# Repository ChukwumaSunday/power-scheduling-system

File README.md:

# Proposal/Report on Power Scheduling Project Using LDR with Arduino Nano for Solar Energy Management

Introduction
Energy management is a crucial aspect of modern office operations, especially with the growing need for sustainable energy solutions. This project outlines the design and implementation of a power scheduling system that uses an Arduino Nano, Light Dependent Resistor (LDR), DS1307 Real-Time Clock (RTC) module, and relays to optimize the use of solar energy in carrying heavy electrical loads during periods of high sunlight intensity. The system also incorporates a 2x16 Liquid Crystal Display (LCD) for real-time data visualization and a user interface with five control buttons for manual adjustments.

Objective
The primary objective of this project is to implement an automated system that shifts heavy electrical loads in an office setting to solar power when sunlight intensity is sufficient. This will minimize dependence on conventional grid power, reduce energy costs, and promote the use of renewable energy.

System Components
1. Arduino Nano: The microcontroller used to process sensor data and control the relays.
2. LDR (Light Dependent Resistor): A sensor used to measure sunlight intensity. The system uses its input to determine when sufficient sunlight is available to switch loads to solar energy.
3. DS1307 RTC Module: Provides accurate time tracking, enabling the system to record start time, date, and manage scheduled tasks.
4. 12V DC Relay and AC Relay: These relays act as switches for controlling the AC-powered heavy loads. The DC relay activates the AC relay, allowing it to handle the higher voltage loads.
5. 2x16 LCD Display: Used for displaying real-time data such as sunlight intensity, load status, and current time.
6. 5-Button Interface (Up, Down, Left, Right, Select): These buttons allow for manual adjustments, navigation of the menu, and control of the system settings.
7. Solar Panel and Battery: The solar panel generates the energy, while the battery stores excess energy for later use.

System Design
The power scheduling system is designed to operate as follows:

												The Schematics

												The Board Layout

												The Board Front View

												The Board Back View

LDR-Based Sunlight Monitoring
The LDR is connected to the Arduino Nano to measure the ambient light intensity. When sunlight is intense enough, typically indicated by an analog voltage value crossing a predefined threshold, the system activates the relays to switch the heavy loads to solar power.

Relay Control
The 12V DC relay is used to switch the AC relay, which controls the connection of heavy electrical loads to the solar power system. When sufficient sunlight is detected, the Arduino activates the DC relay, which in turn energizes the AC relay, allowing heavy office appliances such as air conditioners or industrial lighting systems to run on solar power.

Real-Time Clock for Scheduling
The DS1307 RTC module is employed to keep track of the date and time. This allows the system to monitor power consumption periods, maintain a record of when loads are shifted to solar energy, and ensure that power switching happens during predefined hours of operation. 

The RTC is also crucial for scheduled load management, ensuring that the system operates within the designated timeframes to prevent unnecessary switching during nighttime or low sunlight conditions.

User Interface and LCD Display
The 2x16 LCD displays the current system status, including:
- Sunlight intensity level
- Power source in use (Grid vs. Solar)
- Current date and time from the RTC
- Load status (On/Off)

A 5-button control system allows for easy navigation through the user interface, where the user can manually configure settings such as:
- Sunlight intensity threshold
- Start and stop times for solar-based operation
- Load priorities

Button Functions
- Up/Down Buttons: Used to navigate through menu options.
- Left/Right Buttons: Used to adjust values such as thresholds or time settings.
- Select Button: Used to confirm selections and save settings.

 System Flowchart
1. Initialization: System starts, RTC module initializes, and LCD displays current status.
2. Sunlight Measurement: The Arduino reads LDR values and compares them to the set threshold.
3. Decision Logic:
   - If the sunlight intensity exceeds the threshold, the DC relay is activated to switch the heavy loads to utilizes the solar power.
   - If sunlight intensity is below the threshold, the system defaults to grid power.
4. Manual Override: Users can manually control load settings through the button interface.
5. Scheduled Operation: The RTC module ensures that load switching only occurs within defined operational hours.

Software Implementation
The system software is written in C/C++ and developed using the Arduino IDE. Key sections of the software include:
1. LDR Sensor Data Processing: The LDR provides analog input values, which are converted into digital values for comparison against a predefined threshold.
2. RTC Time Management: The DS1307 module communicates with the Arduino via I2C protocol to maintain accurate time.
3. Relay Control: The Arduino outputs a signal to the DC relay based on the LDR sensor input and the time constraints defined by the RTC module.
4. LCD Display Interface: The LiquidCrystal library is used to manage the 2x16 LCD, allowing for the display of real-time data and system status.
5. Button Interface: Interrupts and debouncing techniques are used to ensure smooth navigation and control via the five-button interface.
Required Components

S/N	COMPONENT	QUANTITY	UNIT PRICE	COST (N)
1	Arduino Nano	1	4,000	4,000
2	BC337	2	50	100
3	6 pins connector	1	200	200
4	7805 Voltage Regulator	1	200	200
5	LED	2	50	50
6	Trim Resistor 10k	2	200	400
7	LDR	1	1,000	1,000
8	12V Adapter	1	2,500	2,500
9	Glossy Paper	4	50	200
10	PCB	1	1,000	1,000
11	DS1307 RTC + CR2032 Cell	1	1,300	1,300
12	12v DC Relay	1	450	450
13	AC  Relay	1	1,500	1,500
14	2x16 LCD	1	2,500	2,500
15	Connecting Wire		2,500	2,500
16	Black Screw	6	50	300
17	Button	5	100	500
18	Resistors	9	20	180
20	Capacitors	4	50	200
21	Male Jumper	1	200	200
22	Female Jumper	1	200	200
23	Blocking Diode	1	50	50
24	Casing/Box	1	1,500	1,500
	Total			21,000

Advantages
- Energy Savings: By utilizing solar energy during peak sunlight hours, the system reduces reliance on grid power, leading to lower energy costs.
- Sustainability: This project promotes the use of renewable energy, contributing to a greener office environment.
- Automation: The system requires minimal human intervention, making energy management more efficient and reliable.
- Cost Efficiency: Once installed, the system reduces operational costs by utilizing free solar energy for heavy loads.

Challenges and Solutions
1. Sunlight Variability: Fluctuating weather conditions may affect sunlight intensity. To address this, the system allows manual configuration of the sunlight threshold via the button interface.
2. Power Backup: In the event of low solar power, the system automatically switches back to grid power, ensuring continuous operation of heavy loads.

Conclusion
This project demonstrates an efficient method for managing power consumption in an office setting by utilizing renewable solar energy when available. Through the use of an LDR, RTC module, relays, and a user-friendly interface, the system provides a cost-effective and environmentally friendly solution for energy management. By incorporating automation and user-configurable settings, the system offers flexibility while promoting sustainability.

The next step is to refine the system with real-world testing to ensure stability and performance in various environmental conditions.

---

This report provides a detailed overview of the system design and operation. If you need further technical details or specific code snippets, let me know!

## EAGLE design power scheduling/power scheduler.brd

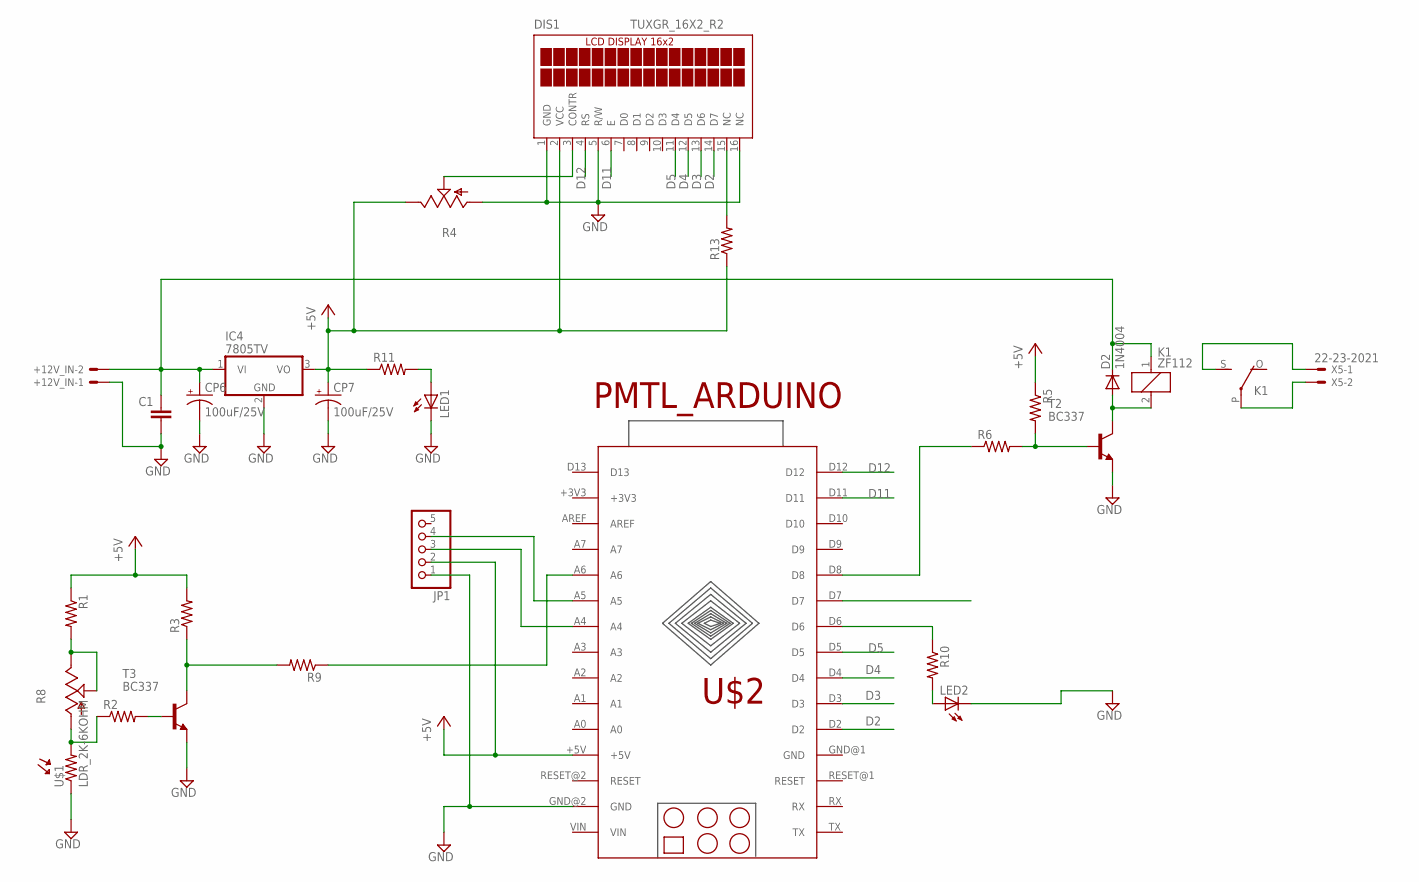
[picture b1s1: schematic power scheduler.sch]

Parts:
+12V_IN: 22-23-2021
C1: C-EU025-025X050; C025-025X050
CP6, CP7: 100uF/25V; E2-5
D2: 1N4004; DO41-10
DIS1: TUXGR_16X2_R2
IC4: 7805TV; TO220V
JP1: PINHD-1X5/90; 1X05/90
K1: ZF112
LED1, LED2: LED3MM
R1, R2, R3, R5, R6, R9, R10, R11, R13: R-US_0204/7; 0204/7
R4, R8: TRIM; 6MM
T2, T3: BC337; TO92
U$1: LDR_2K-6KOHM; XDCR_PDV-P9003-1
U$2: PMTL_ARDUINO
X5: 22-23-2021

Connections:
+5V: CP7.+, DIS1.2 (VCC), IC4.3 (VO), JP1.2, R1.1, R3.2, R4.E, R5.1, R11.1, R13.1, U$2.+5V
D2: DIS1.14 (D7), U$2.D2
D3: DIS1.13 (D6), U$2.D3
D4: DIS1.12 (D5), U$2.D4
D5: DIS1.11 (D4), U$2.D5
D11: DIS1.6 (E), U$2.D11
D12: DIS1.4 (RS), U$2.D12
GND: +12V_IN.1, C1.2, CP6.-, CP7.-, DIS1.1 (GND), DIS1.5 (R/W), DIS1.16 (NC), IC4.2 (GND), JP1.1, LED1.K (C), LED2.K (C), R4.A, T2.1 (E), T3.1 (E), U$1.1, U$2.GND@2 (GND)
unnamed: K1.S, X5.1
unnamed: K1.P, X5.2
unnamed: R2.1, R8.A, U$1.2
unnamed: R1.2, R8.E, R8.S
unnamed: D2.A, K1.2, T2.3 (C)
unnamed: JP1.4, U$2.A5
unnamed: +12V_IN.2, C1.1, CP6.+, D2.C, IC4.1 (VI), K1.1
unnamed: R5.2, R6.2, T2.2 (B)
unnamed: R6.1, U$2.D8
unnamed: R9.1, U$2.A6
unnamed: JP1.3, U$2.A4
unnamed: R2.2, T3.2 (B)
unnamed: R3.1, R9.2, T3.3 (C)
unnamed: LED1.A, R11.2
unnamed: LED2.A, R10.2
unnamed: DIS1.3 (CONTR), R4.S
unnamed: DIS1.15 (NC), R13.2
unnamed: R10.1, U$2.D6

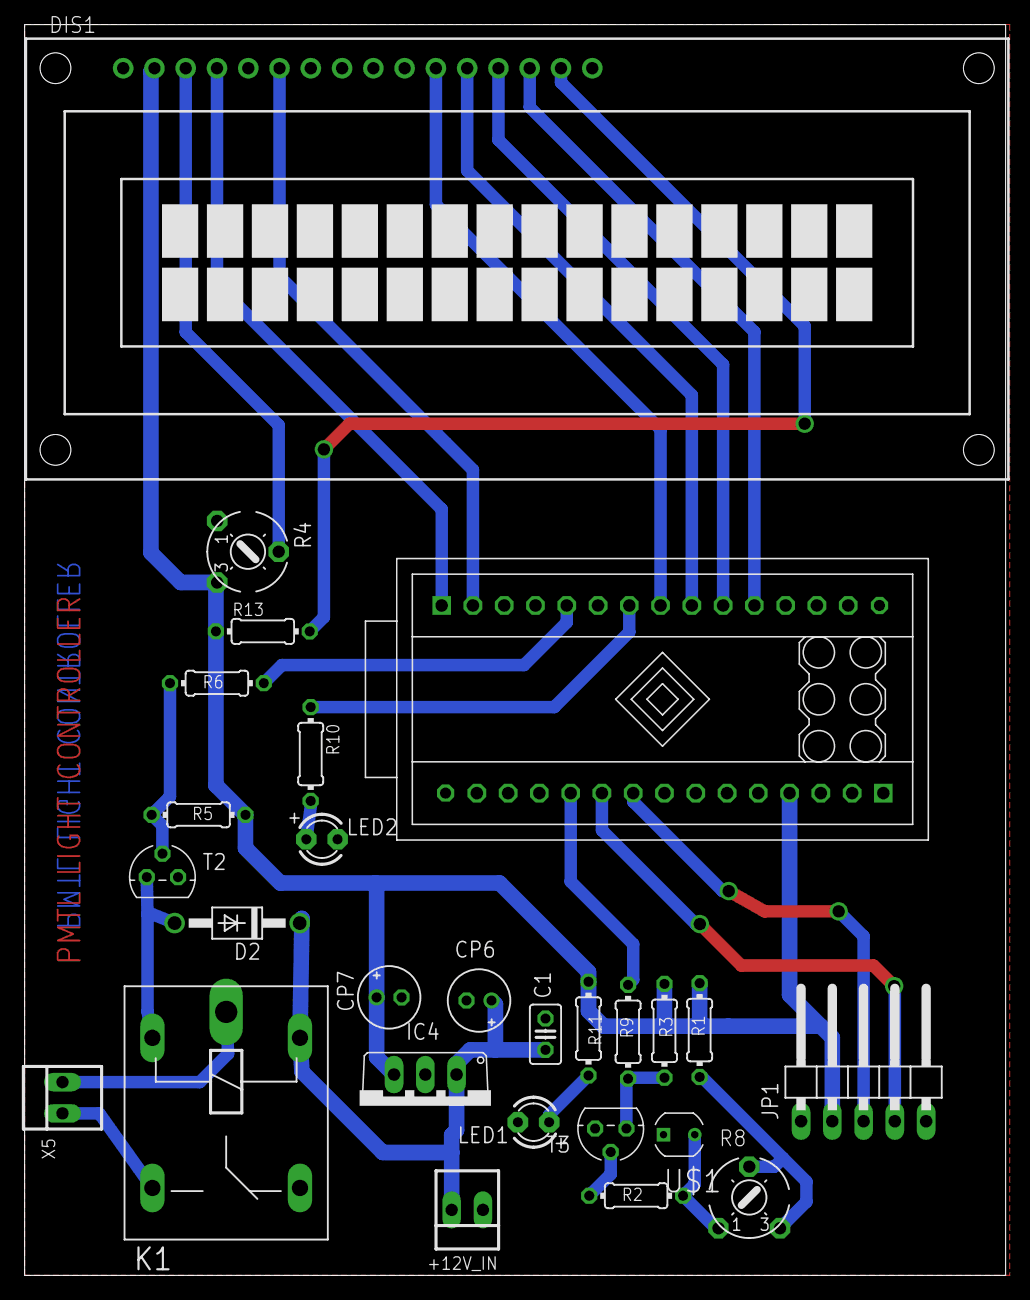
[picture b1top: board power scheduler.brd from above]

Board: 2 copper layers, 79.7 x 101.6 mm, 27 parts (0 on the bottom side), 26 nets.

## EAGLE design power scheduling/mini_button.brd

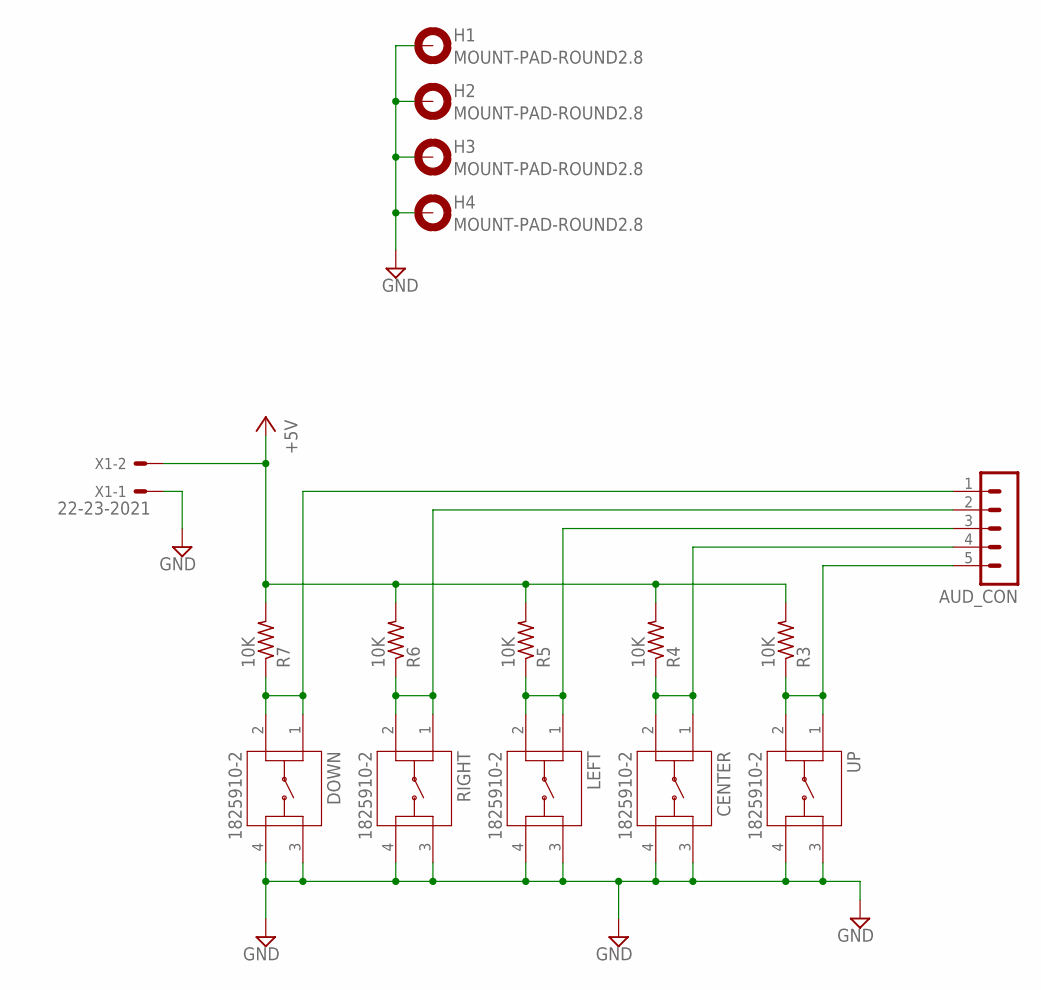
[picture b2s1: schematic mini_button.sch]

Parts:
AUD_CON: MA05-1
CENTER: 1825910-2; TE_1825910-2
DOWN: 1825910-2; TE_1825910-2
H1, H2, H3, H4: MOUNT-PAD-ROUND2.8; 2,8-PAD
LEFT: 1825910-2; TE_1825910-2
R3, R4, R5, R6, R7: 10K; 0204/7
RIGHT: 1825910-2; TE_1825910-2
UP: 1825910-2; TE_1825910-2
X1: 22-23-2021

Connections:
+5V: R3.2, R4.2, R5.2, R6.2, R7.2, X1.2
CENTER: AUD_CON.4, CENTER.1, CENTER.2, R4.1
DOWN: AUD_CON.1, DOWN.1, DOWN.2, R7.1
GND: CENTER.3, CENTER.4, DOWN.3, DOWN.4, H1.B2,8, H2.B2,8, H3.B2,8, H4.B2,8, LEFT.3, LEFT.4, RIGHT.3, RIGHT.4, UP.3, UP.4, X1.1
LEFT: AUD_CON.3, LEFT.1, LEFT.2, R5.1
RIGHT: AUD_CON.2, R6.1, RIGHT.1, RIGHT.2
UP: AUD_CON.5, R3.1, UP.1, UP.2

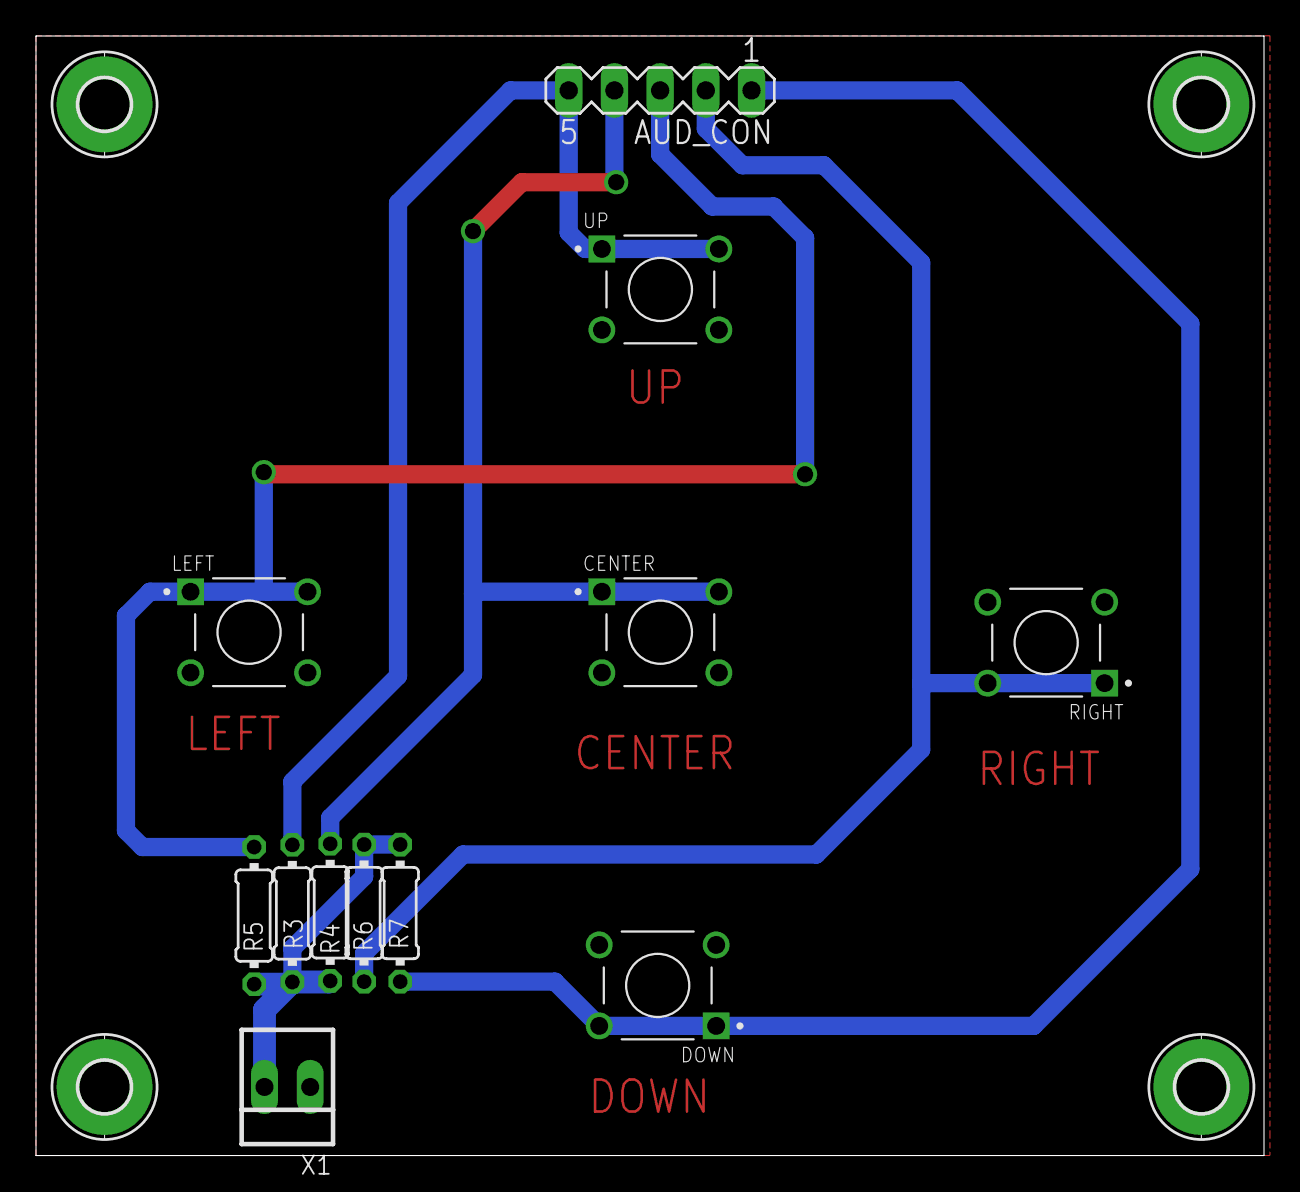
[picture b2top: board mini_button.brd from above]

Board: 2 copper layers, 68.2 x 62.2 mm, 16 parts (0 on the bottom side), 7 nets.

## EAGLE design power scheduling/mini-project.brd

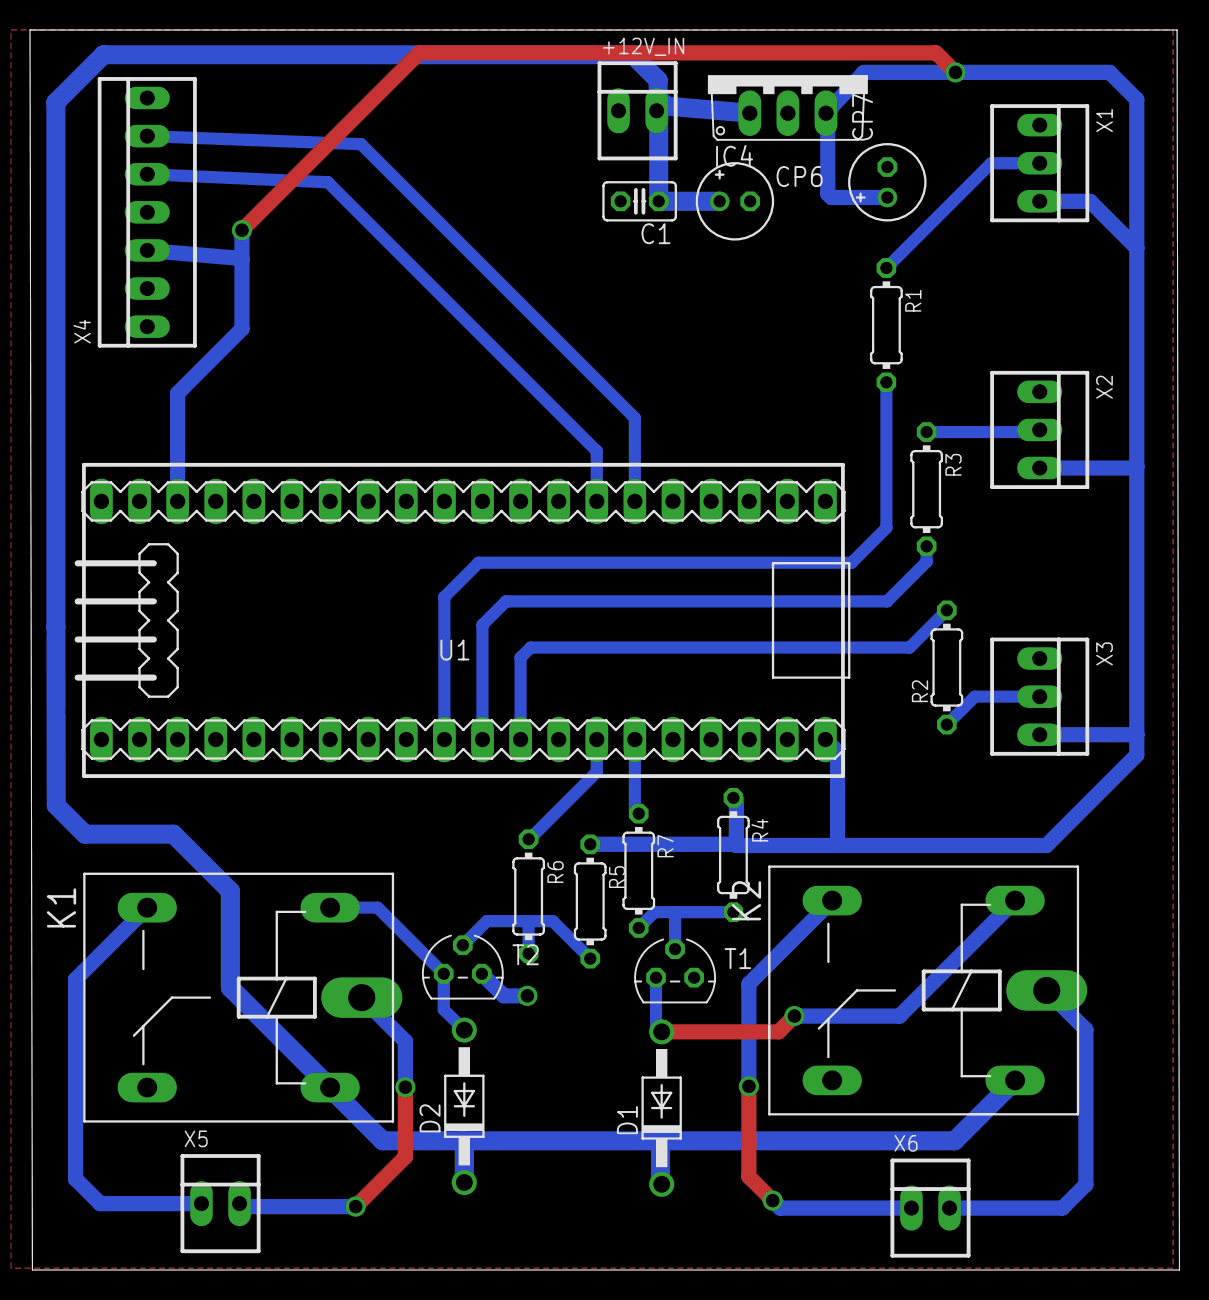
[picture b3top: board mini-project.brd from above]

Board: 2 copper layers, 76.6 x 82.7 mm, 25 parts (0 on the bottom side), 21 nets.

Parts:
+12V_IN: 22-23-2021
C1: C025-025X050
CP6, CP7: 100uF/25V; E2-5
D1, D2: 1N4004; DO41-10
IC4: 7805TV; TO220V
K1, K2: ZF112
R1, R2, R3, R4, R5, R6, R7: 0204/7
T1, T2: BC337; TO92
U1: MCU-STM32F401(BLACK_PEARL)BRD; STM32F401(BLACK_PEARL)BRD
X1, X2, X3: 22-23-2031
X4: 22-23-2071
X5, X6: 22-23-2021

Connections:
+5V: CP7.+, IC4.3, R4.1, R5.1, U1.5V, U1.+5, X1.3, X2.3, X3.3, X4.3
+12V: +12V_IN.2, C1.1, CP6.+, D1.C, D2.C, IC4.1, K1.1, K2.1
GND: +12V_IN.1, C1.2, CP6.-, CP7.-, IC4.2, T1.1, T2.1, U1.G, U1.GND, X1.1, X2.1, X3.1, X4.2, X4.7
unnamed: R1.1, X1.2
unnamed: R3.1, X2.2
unnamed: R2.1, X3.2
unnamed: R1.2, U1.A4
unnamed: R3.2, U1.A5
unnamed: R2.2, U1.A6
unnamed: R5.2, R6.2, T2.2
unnamed: D1.A, K2.2, T1.3
unnamed: D2.A, K1.2, T2.3
unnamed: R4.2, R7.2, T1.2
unnamed: K1.S, X5.1
unnamed: K1.P, X5.2
unnamed: K2.S, X6.1
unnamed: K2.P, X6.2
unnamed: R6.1, U1.B0
unnamed: R7.1, U1.B1
RX: U1.A9, X4.6
TX: U1.A10, X4.5
